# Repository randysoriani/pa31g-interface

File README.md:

# pa31g-interface
Interface board to PA31G Water purifier

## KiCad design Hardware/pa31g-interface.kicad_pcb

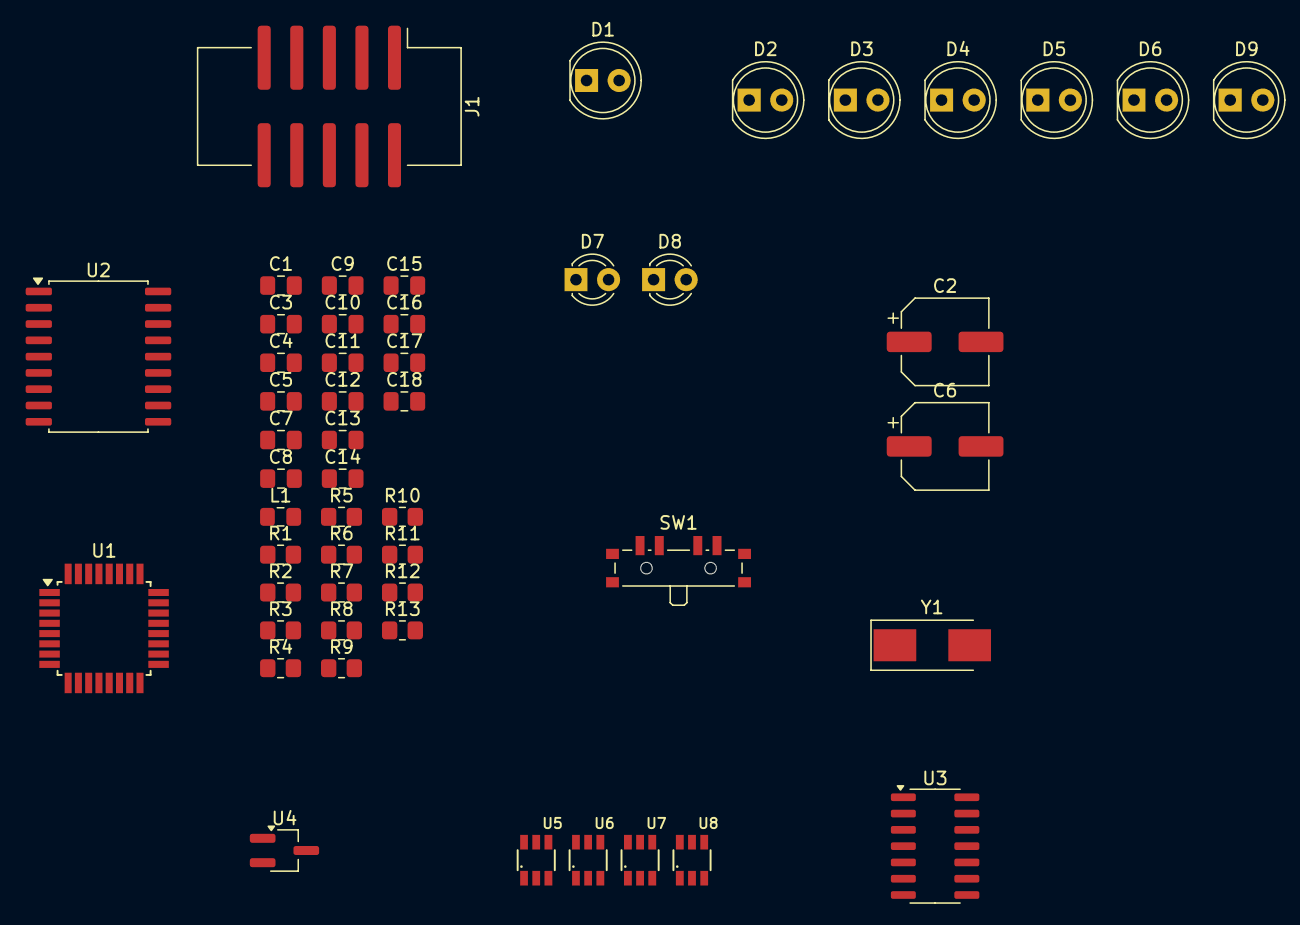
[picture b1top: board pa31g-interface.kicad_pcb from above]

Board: 2 copper layers, 52 parts (0 on the bottom side), 47 nets, no tracks yet.

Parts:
C1, C3, C4, C5, C7, C8, C9, C10, C11, C12, C13, C14, C15, C16, C17, C18: C_Small; C_0805_2012Metric_Pad1.18x1.45mm_HandSolder
C2, C6: C_Polarized_Small_US; CP_Elec_6.3x5.4
D1, D2, D3, D4, D5, D6, D9: LED; LED_D5.0mm_Clear
D7, D8: LED; LED_D3.0mm_Clear
J1: AVR-ISP-10; IDC-Header_2x05_P2.54mm_Vertical_SMD
L1: L_Ferrite_Small; L_0805_2012Metric_Pad1.15x1.40mm_HandSolder
R1, R2, R3, R4, R5, R6, R7, R8, R9, R10, R11, R12, R13: R_Small_US; R_0805_2012Metric_Pad1.20x1.40mm_HandSolder
SW1: SW_MEC_5E; SW_SP3T_PCM13
U1: ATmega8-16A; TQFP-32_7x7mm_P0.8mm
U2: ULN2803A; SOIC-18W_7.5x11.6mm_P1.27mm
U3: 74HC164; SOIC-14_3.9x8.7mm_P1.27mm
U4: uA7805; SOT-23W_Handsoldering
U5, U6, U7, U8: TTP223-BA6; SOT23-6
Y1: Crystal_Small; Crystal_SMD_0603-2Pin_6.0x3.5mm_HandSoldering

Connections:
+5V: C3.1, C5.1, C7.1, C8.1, C9.1, C10.1, C13.1, J1.2 (VCC), L1.1, R1.1, U1.4 (VCC), U1.6 (VCC), U1.18 (AVCC), U3.9 (~MR), U3.14 (VCC), U5.4 (AHLB), U5.5 (VDD), U6.4 (AHLB), U6.5 (VDD), U7.4 (AHLB), U7.5 (VDD), U8.4 (AHLB), U8.5 (VDD)
+5VA: C14.1, L1.2, U1.20 (AREF)
+24V: C1.1, C6.1, U2.10 (COM), U4.1 (IN)
/isp_miso: J1.9 (MISO), U1.16 (PB4)
/isp_mosi: J1.1 (MOSI), U1.15 (PB3)
/isp_sck: J1.7 (SCK), U1.17 (PB5)
/led_sck: U1.27 (PC4), U3.8 (CP)
/led_sda: U1.28 (PC5), U3.1 (DSA), U3.2 (DSB)
/nz_led: R12.2, U1.2 (PD4)
/o_pump_1: U1.12 (PB0), U2.1 (I1), U2.2 (I2), U2.3 (I3)
/o_pump_2: U1.13 (PB1), U2.4 (I4), U2.5 (I5), U2.6 (I6)
/o_touch_1: U1.23 (PC0), U5.1 (Q)
/o_touch_2: U1.24 (PC1), U6.1 (Q)
/o_touch_3: U1.25 (PC2), U7.1 (Q)
/o_touch_4: U1.26 (PC3), U8.1 (Q)
/o_uv_light: U1.14 (PB2), U2.7 (I7), U2.8 (I8)
/p_sens_1: R10.1, U1.22 (ADC7)
/p_sens_2: R11.1, U1.19 (ADC6)
//reset: J1.5 (~RST), R1.2, SW1.3 (K), SW1.4 (A), U1.29 (PC6/~RESET)
GND: C1.2, C2.2, C3.2, C4.2, C5.2, C6.2, C7.2, C8.2, C9.2, C10.2, C11.2, C12.2, C13.2, C14.2, C15.2, C16.2, C17.2, C18.2, J1.4 (GND), J1.6 (GND), J1.8 (GND), J1.10 (GND), R2.1, R3.2, R4.1, R5.2, R6.1, R7.2, R8.1, R9.2, R10.2, R11.2, R13.2, SW1.1, SW1.2, U1.3 (GND), U1.5 (GND), U1.21 (AGND), U2.9 (GND), U3.7 (GND), U4.2 (GND), U5.2 (VSS), U5.6 (TOG), U6.2 (VSS), U6.6 (TOG), U7.2 (VSS), U7.6 (TOG), U8.2 (VSS), U8.6 (TOG)
unnamed: D1.2 (A), U3.3 (Q0)
unnamed: D1.1 (K), R2.2
unnamed: D2.2 (A), U3.4 (Q1)
unnamed: D2.1 (K), R3.1
unnamed: D3.2 (A), U3.5 (Q2)
unnamed: D3.1 (K), R4.2
unnamed: D4.2 (A), U3.6 (Q3)
unnamed: D4.1 (K), R5.1
unnamed: D5.2 (A), U3.10 (Q4)
unnamed: D5.1 (K), R6.2
unnamed: D6.2 (A), U3.11 (Q5)
unnamed: D6.1 (K), R7.1
unnamed: D7.2 (A), U3.12 (Q6)
unnamed: D7.1 (K), R8.2
unnamed: D8.2 (A), U3.13 (Q7)
unnamed: D8.1 (K), R9.1
unnamed: D9.1 (K), R13.1
unnamed: U2.16 (O3), U2.17 (O2), U2.18 (O1)
unnamed: U2.13 (O6), U2.14 (O5), U2.15 (O4)
unnamed: U2.11 (O8), U2.12 (O7)
unnamed: C11.1, U1.7 (PB6/XTAL1), Y1.1
unnamed: C12.1, U1.8 (PB7/XTAL2), Y1.2
unnamed: C2.1, C4.1, U4.3 (OUT)
unnamed: C18.1, U5.3 (I)
unnamed: C15.1, U6.3 (I)
unnamed: C16.1, U7.3 (I)
unnamed: C17.1, U8.3 (I)

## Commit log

2024-09-25 schematic sketch
2024-09-25 add datasheet for main parts
2024-09-26 add some original board as reference
2024-09-26 add some kicad auto generated files
